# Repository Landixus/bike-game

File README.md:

# Arduino Bike Game
[Watch the video demo here](https://youtu.be/r04d039daLk)

My 2015 [High School](http://www.scienceandmathacademy.com/) Capstone Project with mentorship from Christopher Rogers.

### PURPOSE:
To enable a stationary bike to control computer games so that a biker can race in a game while exercising.

### HOW IT WORKS:
The Arduino Leonardo is plugged into a computer where it emulates a keyboard and constantly measures the bike's speed (RPM) and checks that state of the steering.  In the game, the vehicle’s speed and steering are varied by rapidly modulating the arrow key presses sent to the computer by the Leonardo.
For example: if the bike is above the goal RPM (defined as a constant in the code) then it will effectively press the up arrow continously; and at 50% of the goal speed the up arrow will be pressed 50% of the time on average by the Leonardo.

### RESULTS:
* The system is able to control any racing computer game that can be controlled by arrow keys.
* The faster the biker pedals, the faster the race car will go.
* The sharper the biker turns, the sharper the rac car will turn.
* Read the [project poster](https://github.com/danielengbert/bike-game/blob/master/project_poster.pdf) and watch the [video demo](https://youtu.be/r04d039daLk).

### REQUIREMENTS:
* Arduino Leonardo
* custom printed circuit board (see EAGLE CAD files in the PCB folder)
  * and a few resistors and cables
* hall effect sensor
* neodymium magnet
* 1 IR emmiter and 2 IR receivers (serve as a photointerrupter for the steering)
* lazy susan (for the bike's front tire)
* bike and stationary bike stand

### NOTE:
The next phase of this project would be to add capacitive touch sensor to the bike's handlebar for more game control (like activating turbo) and also to add a fan that blows air on the biker at a strength relative to their bike speed.  Preliminary development of this portion of the project was started and built into the PCB.

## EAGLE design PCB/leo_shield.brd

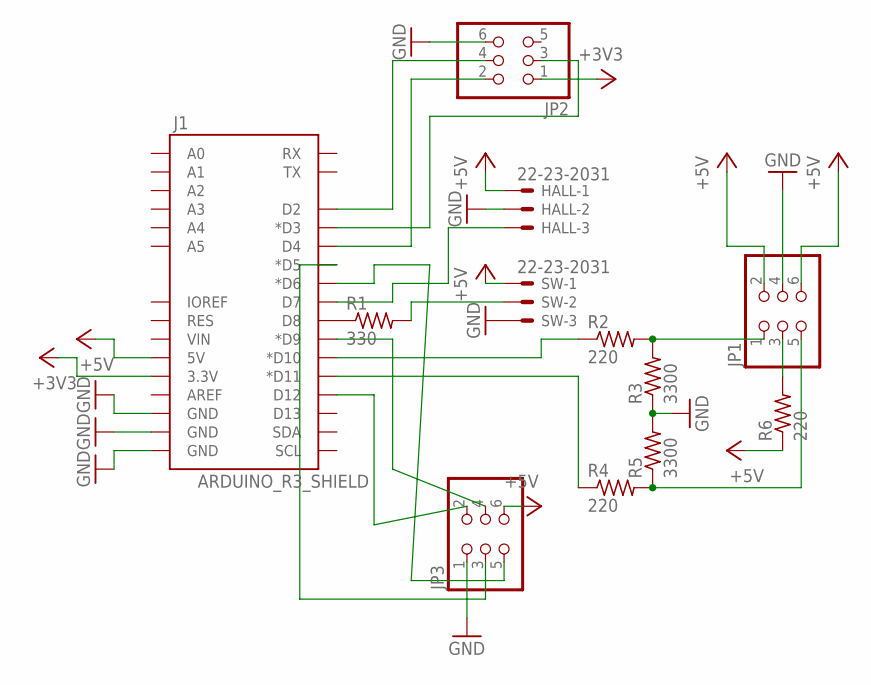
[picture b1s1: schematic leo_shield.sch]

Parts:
HALL: 22-23-2031
J1: ARDUINO_R3_SHIELD; UNO_R3_SHIELD
JP1, JP2, JP3: PINHD-2X3; 2X03
R1: 330; 0204/7
R2, R4, R6: 220; 0204/7
R3, R5: 3300; 0204/7
SW: 22-23-2031

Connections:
+3V3: J1.3.3V, JP2.1
+5V: HALL.1, J1.5V, JP1.2, JP1.6, JP3.6, R6.1, SW.1
GND: HALL.2, J1.GND@0 (GND), J1.GND@1 (GND), J1.GND@2 (GND), JP1.4, JP2.6, JP3.1, R3.1, R5.2, SW.3
IR: JP1.1, R2.2, R3.2
unnamed: J1.D12, JP3.2
unnamed: JP1.3, R6.2
unnamed: R1.2, SW.2
unnamed: J1.D11 (*D11), R4.1
unnamed: J1.D8, R1.1
unnamed: HALL.3, J1.D7
unnamed: JP1.5, R4.2, R5.1
unnamed: J1.D4, JP2.2
unnamed: J1.D2, JP2.4
unnamed: J1.D3 (*D3), JP2.3
unnamed: J1.D10 (*D10), R2.1
unnamed: J1.D9 (*D9), JP3.4
unnamed: J1.D5 (*D5), JP3.3
unnamed: J1.D6 (*D6), JP3.5

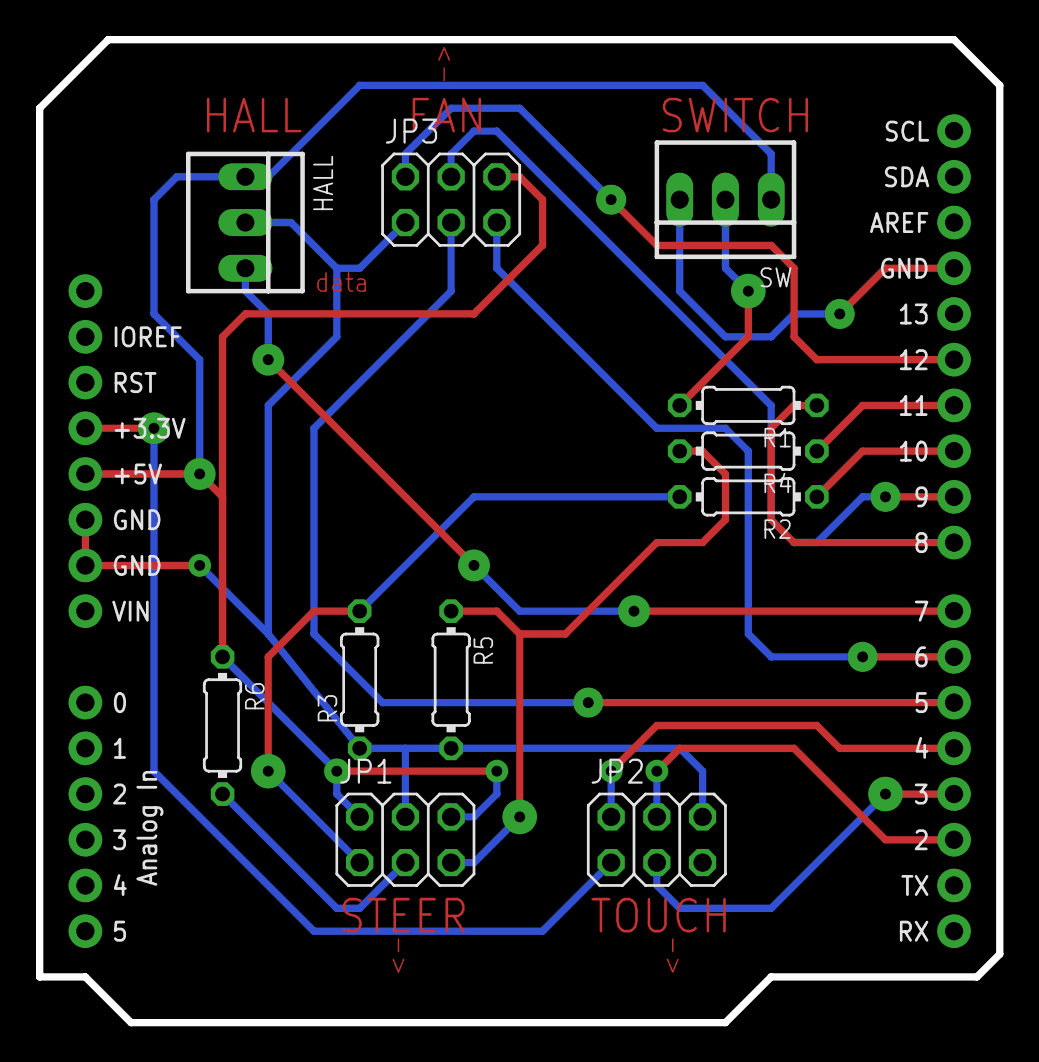
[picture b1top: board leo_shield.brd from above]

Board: 2 copper layers, 53.3 x 54.6 mm, 12 parts (0 on the bottom side), 18 nets.

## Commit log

2017-11-03 Initialized repository with code and PCB files from my 2015 high school project.
2017-11-05 Added some project photos.
2017-11-06 Added project poster (pdf).
2017-11-06 Added steering pattern
2018-09-23 Added project video.
2018-09-23 Changed video permissions (removed executability).

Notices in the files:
parts and their libraries:
SparkFun-Boards: Licensing: Creative Commons ShareAlike 4.0 International - https://creativecommons.org/licenses/by-sa/4.0
